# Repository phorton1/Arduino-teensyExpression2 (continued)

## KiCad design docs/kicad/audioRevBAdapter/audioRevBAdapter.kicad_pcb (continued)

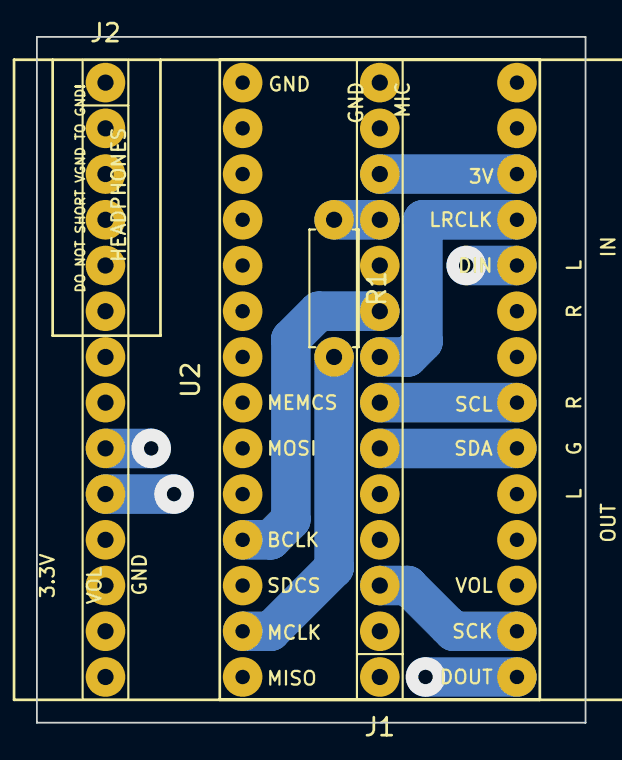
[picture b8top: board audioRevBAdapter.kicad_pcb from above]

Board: 2 copper layers, 30.5 x 38.1 mm, 4 parts (0 on the bottom side), 11 nets.

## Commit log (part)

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2023-08-08 added mem_check, buttons, and bare bones system
2023-08-08 start adding midiQueue
2023-08-08 added midiQueue, ftp, buttons, pedals, and rotaries took 50K (20%) of RAM!
2023-08-08 added const default_prefs and Pedal Names, made prefs write 255 if byte matches default
2023-08-08 turned on theSystem drawing
2023-08-08 tested Pedals and Rotaries with minor bug fix
2023-08-08 Normalize Looper commonDefines.h
2023-08-09 prepare to start writing rigParsers
2023-08-09 added fileSystem and implemented rigParser
2023-08-11 rig parser WIP
2023-08-12 new rigParser generates code; rigDump.h dumps it; added all operators; ready for expressions
2023-08-13 bug fixes and test code before doing expressions
2023-08-13 restructure rigParser & rigDump
2023-08-13 rigExpression parsing and dumping finished
2023-08-15 added rig DEFINES, which work in button_statements (not yet in init_statements)
2023-08-15 Generalized parametrized init Statements
2023-08-17 rig expression evaluator and first statement execution
2023-08-17 check VALUE[] and STRING[] indexes, and return "" for undefined STRING{}'s
2023-08-17 rigMachine.cpp - added most statements
2023-08-18 switch to new myLCD library (formerly LCDWIKI_GUI and KBD)
2023-08-19 add examples (test programs)
2023-08-19 fix compiler warning
2023-08-19 FIRST TEENSY 4.1 COMPILE - temporarily moved usb_desc.c and _prh.h to data directory
2023-08-19 FIRST TEENSY 4.1 COMPILE - __bss_start not defined
2023-08-19 FIRST TEENSY 4.1 COMPILE - update to new (teensyDuino) SdFat library
2023-08-20 FIRST TEENSY 4.1 COMPILE - checkin preferences.txt and teensyDuino.md doc
2023-08-20 recompiled for teensy3.6 - implemented new _usbNames.c
2023-08-20 added ili9488 test program - works with all teensy 3.6's I have
2023-08-20 moved cmem_check.cpp to /src and used __IMXRT1062__ to temporariliy #ifdef things out that didn't compile on Teensy 4.1
2023-08-20 PREPARE for NEW mother_board and display connector ON old teensyExpression box - cleaned up pin definitions - added connector comments - note that rotararies are probably in wrong order and/or revers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
2023-08-21 FIXED LCD_DATA pin order; use revamped myLCD API method names
2023-08-22 update test programs to new TFT pin defines
2023-08-22 preferences.txt
2023-08-22 added sdStart test program (proves new SdFat 2.1.2 library does not work after compile/upload)
2023-08-22 INO & theSystem.cpp - slight cleanup - no significant changes
2023-08-22 USE_OLD_FAT define used in fileSystem.cpp and h and implicitly in rigToken.cpp
2023-08-22 theSystem.cpp turn on default rig load at boot; rigMachine.cpp cleanup order of methods
2023-08-23 correct ROTARY defines for old perf rotary board and new TE pcb motherboard
2023-08-24 Cleaned up defines.h and copied PIN assignments to old teensyExpression
2023-08-24 IT'S WORKING!! First successful text driven rig WORKS with the existing Looper and iPad system. - simplified BUTTONS, which are now responsible for their LEDs - cleaned up and added debugging to midi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
2023-08-25 implement button blink; cleanup dbg constants, rename aSystem to theSystem and remove #ifdef 0's
2023-08-25 made PARAM_MIDI_CHANNEL enforce 1..16, added PARAM_LISTEN_CHANNEL, which allows 0, cleaned up sendMidiMsg stuff in prep for really understanding ports
2023-08-25 EEPROM - check/write 238 to EEPROM 0 to identify teensyExpression2 and automatically reset prefs if not
2023-08-26 basic PORTS figured out. Need in rigToken on up .... then on to monitorings
2023-08-26 updated rigParser to new MIDI_PORTS
2023-08-26 implemented PEDALS and ROTARIES to use correct PORTS; added MIDI_TYPES
2023-08-26 changed FTP_ENABLE to FTP_PORT and added SPOOF_FTP pref
2023-08-26 implemented Off,IN,OUT,Both for MONITOR_PORT prefs
2023-08-27 added rig relocate() method
2023-08-28 implmented MODAL_RIGS
2023-08-29 implemented MODAL rigs and dumpRigCode() and loading of default rig from constants
2023-08-29 cleaned up const rig_t's and loading
2023-08-29 cleaned up rigDumpCode.cpp and generally got a good version of const rig handling
2023-08-29 fixed bad rotary numbers in default.rig
2023-08-30 rework monitor port prefs
2023-08-30 change to 3 sets of midi indicators
2023-08-30 implement midi queue (1)
2023-08-30 move old stuff in defines.h down
2023-08-30 added critical_timer_handler() and outgoing message queue to re-make initFTPQuery() into asynch functionality; removed WITH_MIDI_HOST define introduce myDebug "debug_level" macro
2023-08-30 Implemented sysWindows stack and the winFtpTuner
2023-08-30 implemented ftpSensitivity (and moved buttons.task() out of timer_handler())
2023-08-31 got rid of heap usage by rigParser. protected dbgSerial. fixed some comments
2023-08-31 implemented FOLLOWS DEBUG_DEVICE for FILE_SYSTEM_DEVICE and fairly major cleanup and bug searching session
2023-08-31 added RIG_NAME and ROTAARY NAME to prefs and code in prep for implementing config
2023-08-31 implemented rigErrorDialog and asynchronos loadRig() also implemented yesNoDialog and touched all the_buttons and the_pedals references
2023-09-01 clean up INO setup() method
2023-09-01 remove ftp_port param from sendFTPCommandAndValue()
2023-09-02 intial config window
2023-09-02 DEFAULT_PREFS fix for uint16_t's and string's in preparation for more winConfig work
2023-09-03 added winConfigPedal & changed winConfig to show if prefs have change (BLUE/GREEN vs ORANGE/PURPLE)
2023-09-03 fixed minor bugs in rigMachine::onMidiCC()
2023-09-03 comments and minor corrections
2023-09-03 minor change to default rig
2023-09-03 implemented winFileDialog and usage to Load Rigs from prefs including ability to back out of changes after trying them implmented DUMP_H_FILES pref and usage to call dumpRigCode() to allow users to l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
2023-09-04 added rigFileDialog as a better 'fix' so there's no problem with onChildEnd() popping up other windows.
2023-09-04 yet another cleanup of endModal(), winConfig rig loading, and dumping of H files
2023-09-04 improved fileSystem debugging and increased GET buffer sizes
2023-09-04 Looper V2.11 - rewrote handleSerialMidi() and implemented LOOP_COMMAND_GET_STATE at default rig startup - got rid of wait loops on INO serial startups - moved call to new handleSerialData() to critic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
2023-09-05 fixed double rig_error reporting
2023-09-05 new rigs in preparation for major parser rewrite
2023-09-05 MAJOR REWORK OF RIG LANGUAGE tokens, parser, and machine - sanity checkin before Meters, Ranged buttons, _BUTTON_NUM param, and Constant Folding in expressions
2023-09-06 MAJOR WORK - sanity checkin - working new RIGS and LANGUAGE
2023-09-07 lotsa changes - added INPUT/OUTPUT/BOTH filtering to LISTEN statements
2023-09-07 implemented RANGED_LISTENS, _BUTTON_ROW, and _BUTTON_COL trying to get new rig working completely, ran into order of operations issue in evaluator
2023-09-08 EVALUATOR - doOps of equal precedence in LEFT-TO-RIGHT order
2023-09-08 reworked RANGED_BUTTONS so that there is only one set of statements and expressions generated making the memory foot print of rigs MUCH smaller at hardly any performance compromise
2023-09-08 comment only changes to rig files
2023-09-08 added RIG_TOKEN_SETITITLE statement and implementation use setTitle() in default_modal rig to show the Track NUMBER changed default_modal to use clicks for MUTE and LONG PRESS to change selected_trac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
2023-09-08 RIGS DONE!! MILESTONE CODE CLEANUP - added ok dialog to dump H files default.rig and default_modal.rig are pretty much complete!!
2023-09-09 implemented Rotary listening for TE control changes so knobs don't jump
2023-09-09 improved Rig Statement and Code Error reporting shows line_num and param_num
2023-09-11 fileSystem.cpp - WIP on buddy & apps/file2
2023-09-13 updated preferences.txt to try to avoid stomping on teensyPiLooper
2023-09-13 added real Teensy USB Serial Number to my USB stuff
2023-09-16 revert back to simpler buddy console app with fileServer - still having problems with closing things and exiting loops
2023-09-17 added songs/ to data/ for testing fileSystem
2023-09-18 comments and debugging only
2023-09-18 fileSystem.cpp - implemented REMOTE delete (wihtout PROGRESS)
2023-09-19 implemented PROGRESS dialog and packet handling
2023-09-19 fileSystem; implemented threaded fileSystem::threads.addThread(fileSystem::handleFileCommand() using TeensyThreads many concerns. See /Pub/FS/readme.md for more info
2023-09-20 changed structure of file_commands and optimized theSystem::handleSerialData();
2023-09-20 turned off TEST_DELAY
2023-09-22 FS,buddy,TE::fileSystem.cpp - implmented ABORT for asynchronous remote file_requests
2023-09-24 Restructure FileSystem #101
2023-09-26 implemented new teensy fileCommand serial queue scheme with bug fixes, comments, and updated docs
2023-09-28 prep for chainging file_reply: to single packet
2023-09-29 FIXED "MALLOC() DOESNT WORK IN TEENSYTHREADS" PROBLEM
2023-09-29 implemented single line file_replies tween teensy and Perl
2023-09-29 implemented basic TE fileCommand(FILE)
2023-09-30 implemented local PUT empty dirs and PUT dirs with timestamps
2023-10-01 finished fileSystem (implemented PUT command)
2023-10-01 minor fixes to FILE behaviors
2023-10-02 implemented SERVER_IDs and reworked a LOT of code around threadedCommands, forking, and threading
2023-10-03 fileSystem.cpp : turned on added more debugging during initFileSystem()
2023-10-03 implemented WITH_LOCAL_PROGRESS defines and code for progress notifications for BASE64 and FILE commands
2023-10-03 initial commit of fileFormat.cpp (formats SD cards)
2023-10-10 added LICENSE.TXT and empty docs/readme.md to most public repositories
2023-11-02 fix broken links across all repos with introduction of base-apps-gitUI::repoDocs.pm
2024-04-05 added initial "integrated.md" and "row_board" and "integrated" kicad stuff
2024-04-21 added lcd_connector x 4 to teensyExpression2
2024-04-29 working definition of teensyExpression3 rPi pin usage
2024-04-29 minor cleanup docs/kicad
2024-05-06 pushing all intermediate teensyExpression3 kicad designs, symbols, footprints, etc
2024-05-06 starting new teensyExpression3/Arduino-teensyPiAudio repositories/projects.
2024-05-06 updated date in doc
2024-05-07 updated (now obsolete) audioBoard PCB and removed plot files
2024-05-11 added .gitignore to all TE related doc/kicad folders. Renamed and moved kicad designs around. See /junk/maybe_save for remnants
2024-05-12 updated kicad .gitignore's
2024-05-28 accurate pinOuts in mother_board.sch and rants on sgtl5000 audio problems in audio.md
2024-05-28 pushing intermediate and messy TE3 vGuitar system kicad designs
2024-05-29 got rid of 1 obsolete kicad design
2024-05-29 added (yet another) teensyExpression2 _prototype1 kicad design for esp32-rpi-sgtl5000 testing
2024-05-30 added te2/docs/kicad/_rpi_hat tentaive PCB design
2024-06-10 add _overview hierarchial kicad design
2024-07-17 checkin dangling teensy Expression nested schematic attempt
2025-01-09 fix minor connection on future row_board
2025-01-12 convert teensyExpression1 to myLCD library & remove LCD_WIKI stuff - also moved test programs out of teensyExpression2
2025-01-14 changed to rotation 3 in newly rebuilt and printed TeensyExpression Box
2025-01-14 added unix MODE,OWNER,GRIUP zeros to file replies to get TE2 working with new fileClient & buddy
2025-01-14 temporary setting of default debug device to USB for new TE box testing
2025-01-14 fix bug in fileUtils.cpp::getNextEntry() - START NORMALIZING fileXXXX.h and cpp
2025-01-14 Manually normalized fileXXXX.cpp & h files between TE1 and TE2 in prep for some bug-fix rework ...
2025-01-16 completly reworked COMMON TE1 and TE2 fileXXXX h and cpp and mem_check.cpp files
2025-01-17 built and tested new TE Rotary Board
2025-01-17 fix typo in doc only
2025-01-17 mem_check.cpp: change printf() to Serial.printf() only
2025-01-17 midiQueue.cpp: change inner debug message to "do" enqueueMidi only
2025-01-18 DON'T LIKE IT - I'M GONNA OBSOLETE THIS REPO - checked in change to rigs to fix obscure interrupt/timing problem in "quick mode"
2025-01-22 remove mem_check.cpp issues on teensy4.1
